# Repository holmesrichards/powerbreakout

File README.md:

# Euro/Kosmo power breakout

A little board (30 x 36 mm) for connecting Eurorack or Kosmo power distribution systems to non Euro/Kosmo module PCBs. Footprints are provided for a 2x5 shrouded pin header to connect to the bus board, and a 3 pin terminal block to connect to the module PCB. (Of course one could instead solder wires to the terminal block pads.) Footprints are also provided for electrolytic capacitors from the rails to ground, and for Schottky diodes (or fuses or 10Ω resistors or ferrite beads or whatever you prefer) between the pin header and the rails, in case these are not provided for on the module PCB. If they are, the capacitors can be omitted and there are solder jumpers that can be filled to bypass the diode pads.

[Schematic, such as it is](Docs/powerbreakout.pdf) 

[BOM](Docs/powerbreakout_bom.md)

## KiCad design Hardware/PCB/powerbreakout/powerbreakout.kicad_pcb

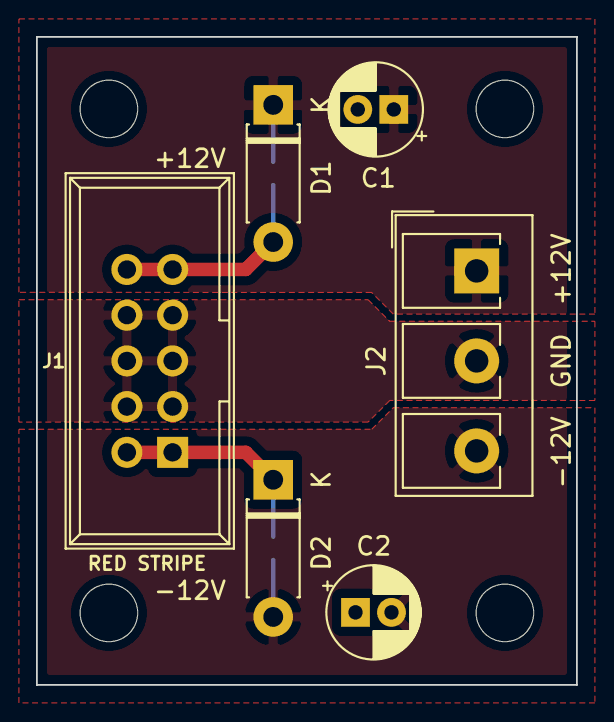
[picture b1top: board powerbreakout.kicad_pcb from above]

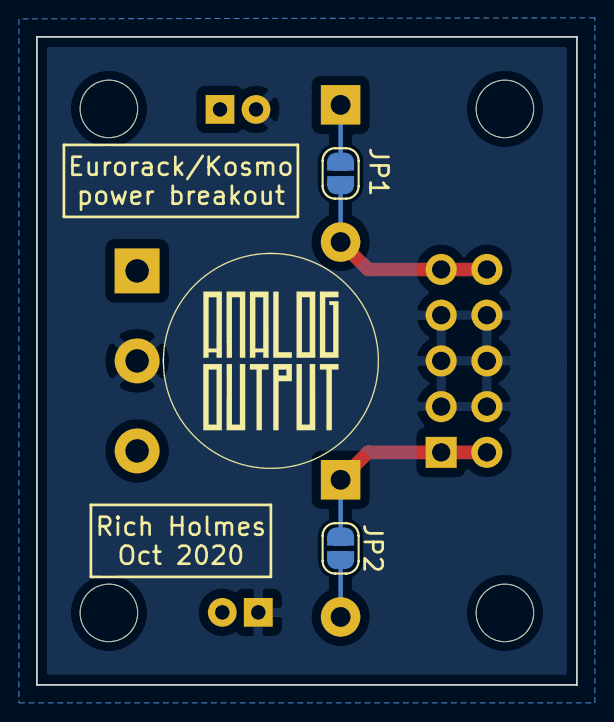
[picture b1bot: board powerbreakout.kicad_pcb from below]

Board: 2 copper layers, 30.0 x 36.0 mm, 8 parts (2 on the bottom side), 5 nets.

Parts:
C1, C2: 10uF; CP_Radial_D5.0mm_P2.00mm
D1, D2: D_Schottky; D_DO-41_SOD81_P7.62mm_Horizontal
J1: Synth_power_2x5; Power_Header
J2: Screw_Terminal_01x03; TerminalBlock_Degson_DG301_1x03_P5.00mm_Vertical
JP1, JP2: SolderJumper_2_Open; SolderJumper-2_P1.3mm_Open_RoundedPad1.0x1.5mm

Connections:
+12V: C1.1, D1.1, J2.1, JP1.2
-12V: C2.2, D2.2, J2.3, JP2.2
GND: C1.2, C2.1, J1.3, J1.4, J1.5, J1.6, J1.7, J1.8, J2.2
unnamed: D1.2, J1.9, J1.10, JP1.1
unnamed: D2.1, J1.1, J1.2, JP2.1

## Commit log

2020-11-21 Create LICENSE
2020-12-01 Updated Gerbers
2020-12-14 Add Tayda numbers to BOM
2020-12-14 PCB silk/fab/courtyard tweaks
2021-01-02 Footprints updated
2021-01-17 Include lib table files
2021-02-19 Footprint update
2021-02-28 Update .gitignore, DIN5
